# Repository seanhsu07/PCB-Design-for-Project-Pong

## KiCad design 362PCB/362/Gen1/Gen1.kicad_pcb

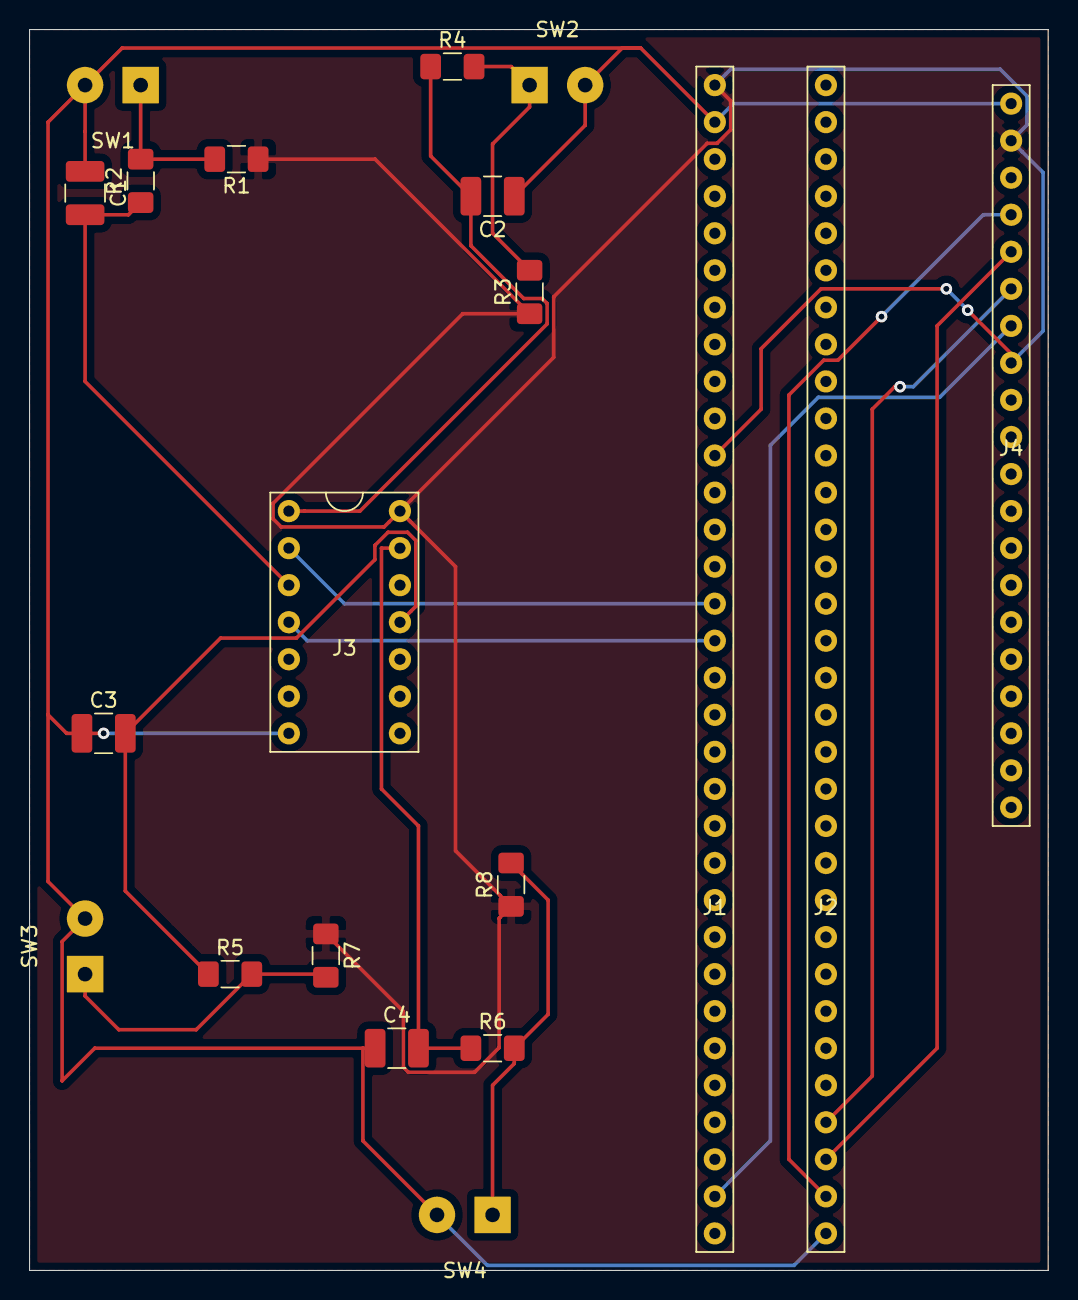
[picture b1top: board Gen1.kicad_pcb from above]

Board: 2 copper layers, 69.8 x 85.1 mm, 20 parts (0 on the bottom side), 17 nets.

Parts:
C1, C2, C3, C4: C; C_1210_3225Metric_Pad1.42x2.65mm_HandSolder
J1: STM32Left; STM32conn
J2: STM32Right; STM32conn
J3: Conn_02x07_Odd_Even; HC14
J4: LCD
R1, R2, R3, R4, R5, R6, R7, R8: R; R_1206_3216Metric_Pad1.42x1.75mm_HandSolder
SW1, SW2, SW3, SW4: SW_Push; SolderWirePad_1x02_P3.81mm_Drill1mm

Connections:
+3V3: J1.1, J3.2, J4.19, R1.1, R3.1, R7.1, R8.1
GND: C1.1, C2.1, C3.1, C4.1, J1.2, J2.32, J3.13, J4.20, SW1.2, SW2.2, SW3.2, SW4.2
unnamed: C1.2, J3.5, R2.1
unnamed: C2.2, J3.1, R4.1
unnamed: C3.2, J3.8, R5.1
unnamed: C4.2, J3.4, R6.1
unnamed: R1.2, R2.2, SW1.1
unnamed: R3.2, R4.2, SW2.1
unnamed: R5.2, R7.2, SW3.1
unnamed: R6.2, R8.2, SW4.1
PA0: J1.15, J3.3
PA1: J1.16, J3.7
PB12: J1.31, J4.14
PB13: J2.31, J4.17
PB14: J2.30, J4.16
PB15: J2.29, J4.15
PC2: J1.11, J4.13

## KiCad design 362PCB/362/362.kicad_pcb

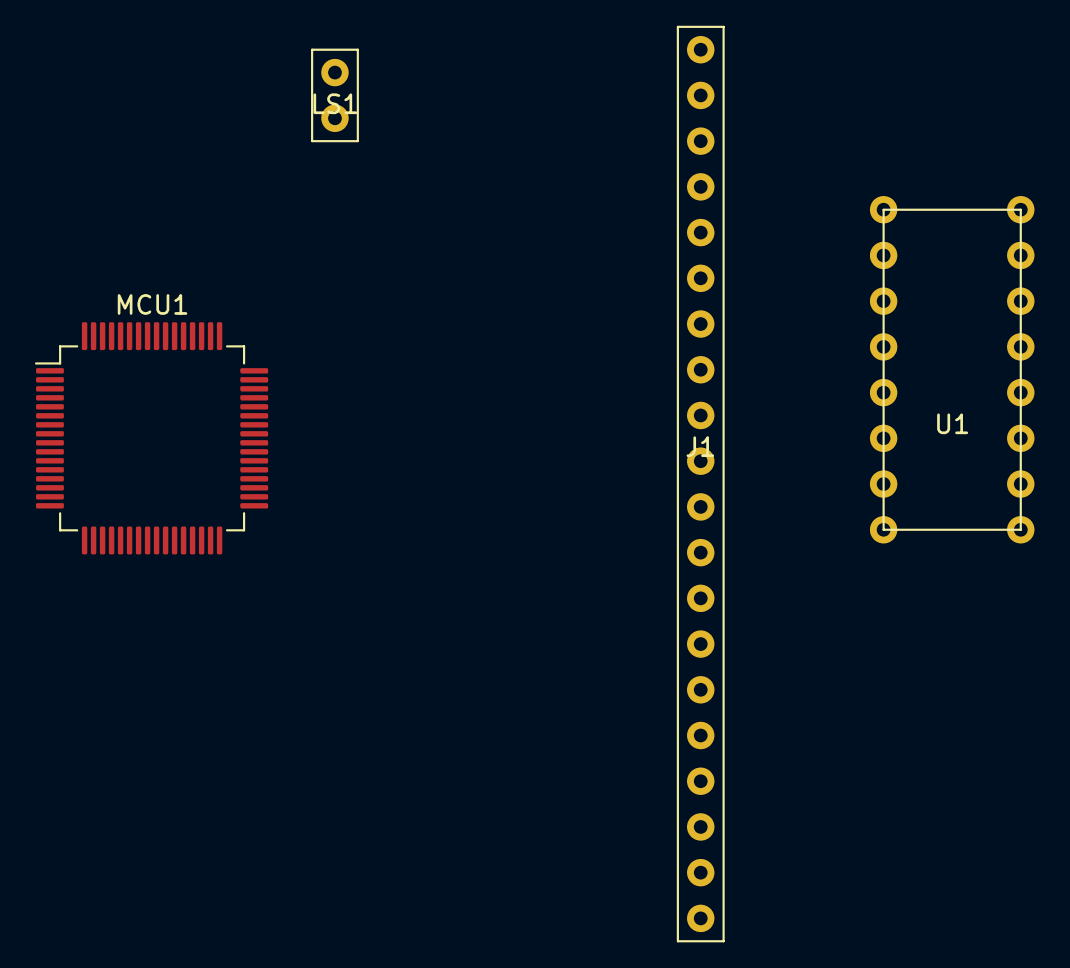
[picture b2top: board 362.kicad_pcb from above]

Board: 2 copper layers, 4 parts (0 on the bottom side), 3 nets, no tracks yet.

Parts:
J1: Conn_01x20_Female; J1
LS1: Speaker; SPK
MCU1: STM32F051R8Tx; LQFP-64_10x10mm_P0.5mm
U1: CFAL1602C; CFAL

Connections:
GND: J1.20, LS1.2, MCU1.12, MCU1.31, MCU1.63
PA4: J1.14, LS1.1, MCU1.20
VDD: J1.18, MCU1.32

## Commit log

2019-05-14 Add files via upload
    All kicad files
